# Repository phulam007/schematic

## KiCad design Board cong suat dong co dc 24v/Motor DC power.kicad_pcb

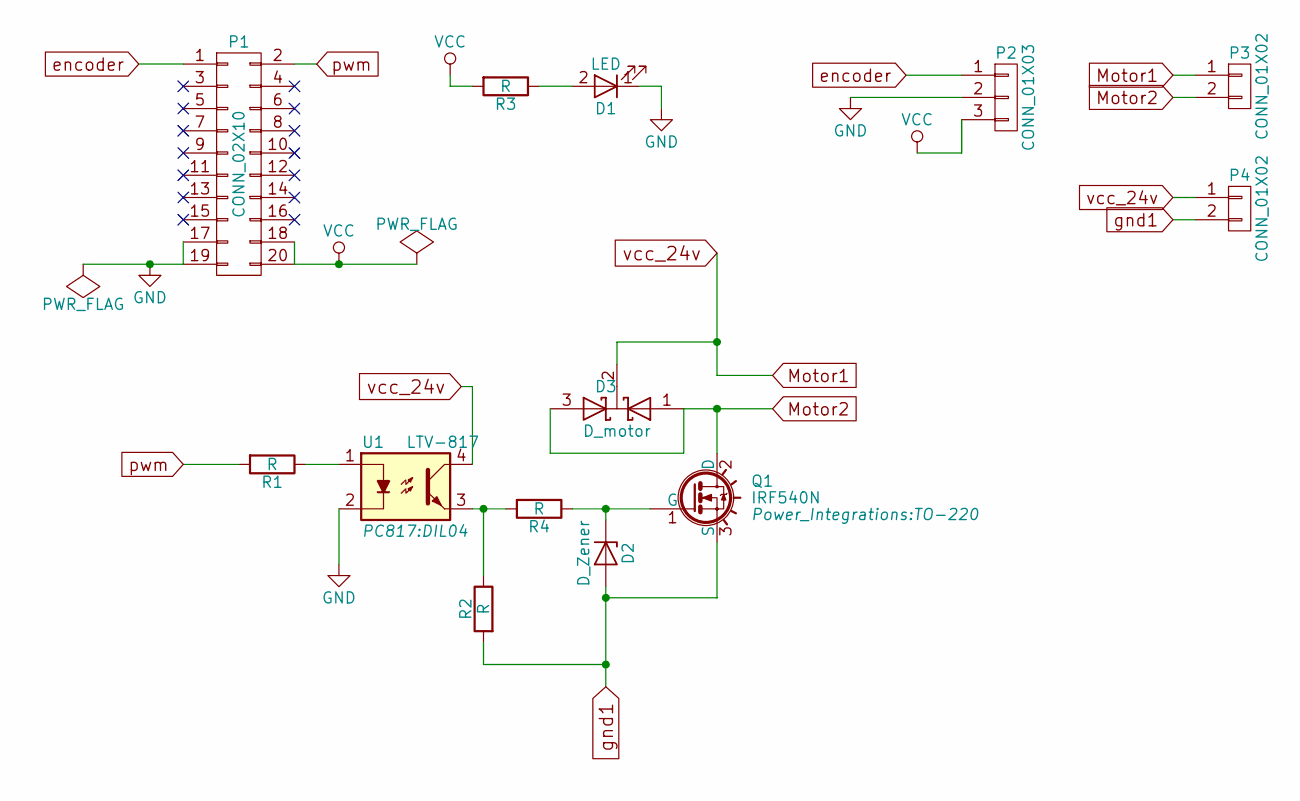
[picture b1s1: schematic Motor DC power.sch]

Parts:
D1: LED; LED_D3.0mm
D2: D_Zener; R_Axial_DIN0207_L6.3mm_D2.5mm_P7.62mm_Horizontal
D3: D_motor; TO-220
P1: CONN_02X10; IDC-Header_2x10_Pitch2.54mm_Straight
P2: CONN_01X03; TerminalBlock_bornier-3_P5.08mm
P3, P4: CONN_01X02; TerminalBlock_bornier-2_P5.08mm
Q1: IRF540N; TO-220
R1, R2, R3, R4: R; R_Axial_DIN0207_L6.3mm_D2.5mm_P7.62mm_Horizontal
U1: LTV-817; DIL04

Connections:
GND: D1.1 (K), P1.17, P1.19, P2.2, U1.2
Motor1: D3.2 (K), P3.1, P4.1, U1.4
Motor2: D3.1 (A), D3.3 (A), P3.2, Q1.2 (D)
unnamed: D1.2 (A), R3.1
unnamed: D2.1 (K), Q1.1 (G), R4.1
unnamed: R1.1, U1.1
unnamed: R2.1, R4.2, U1.3
VCC: P1.18, P1.20, P2.3, R3.2
encoder: P1.1, P2.1
gnd1: D2.2 (A), P4.2, Q1.3 (S), R2.2
pwm: P1.2, R1.2

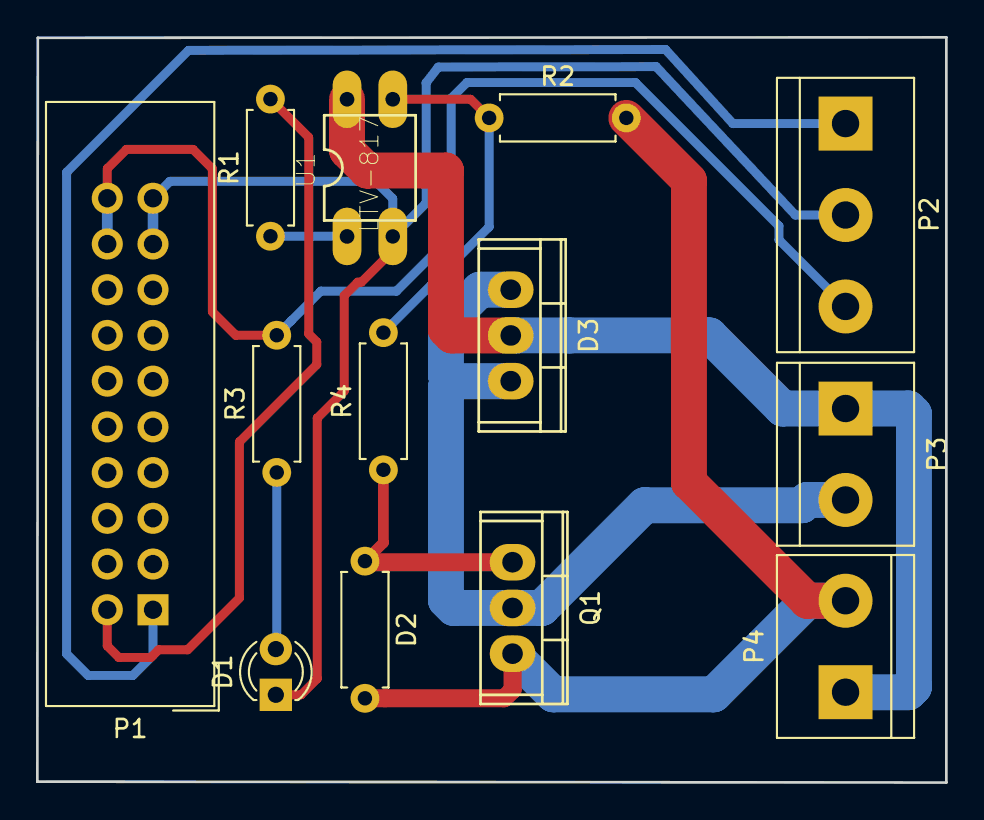
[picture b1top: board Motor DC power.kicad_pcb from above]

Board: 2 copper layers, 50.5 x 41.4 mm, 13 parts (0 on the bottom side), 11 nets.
